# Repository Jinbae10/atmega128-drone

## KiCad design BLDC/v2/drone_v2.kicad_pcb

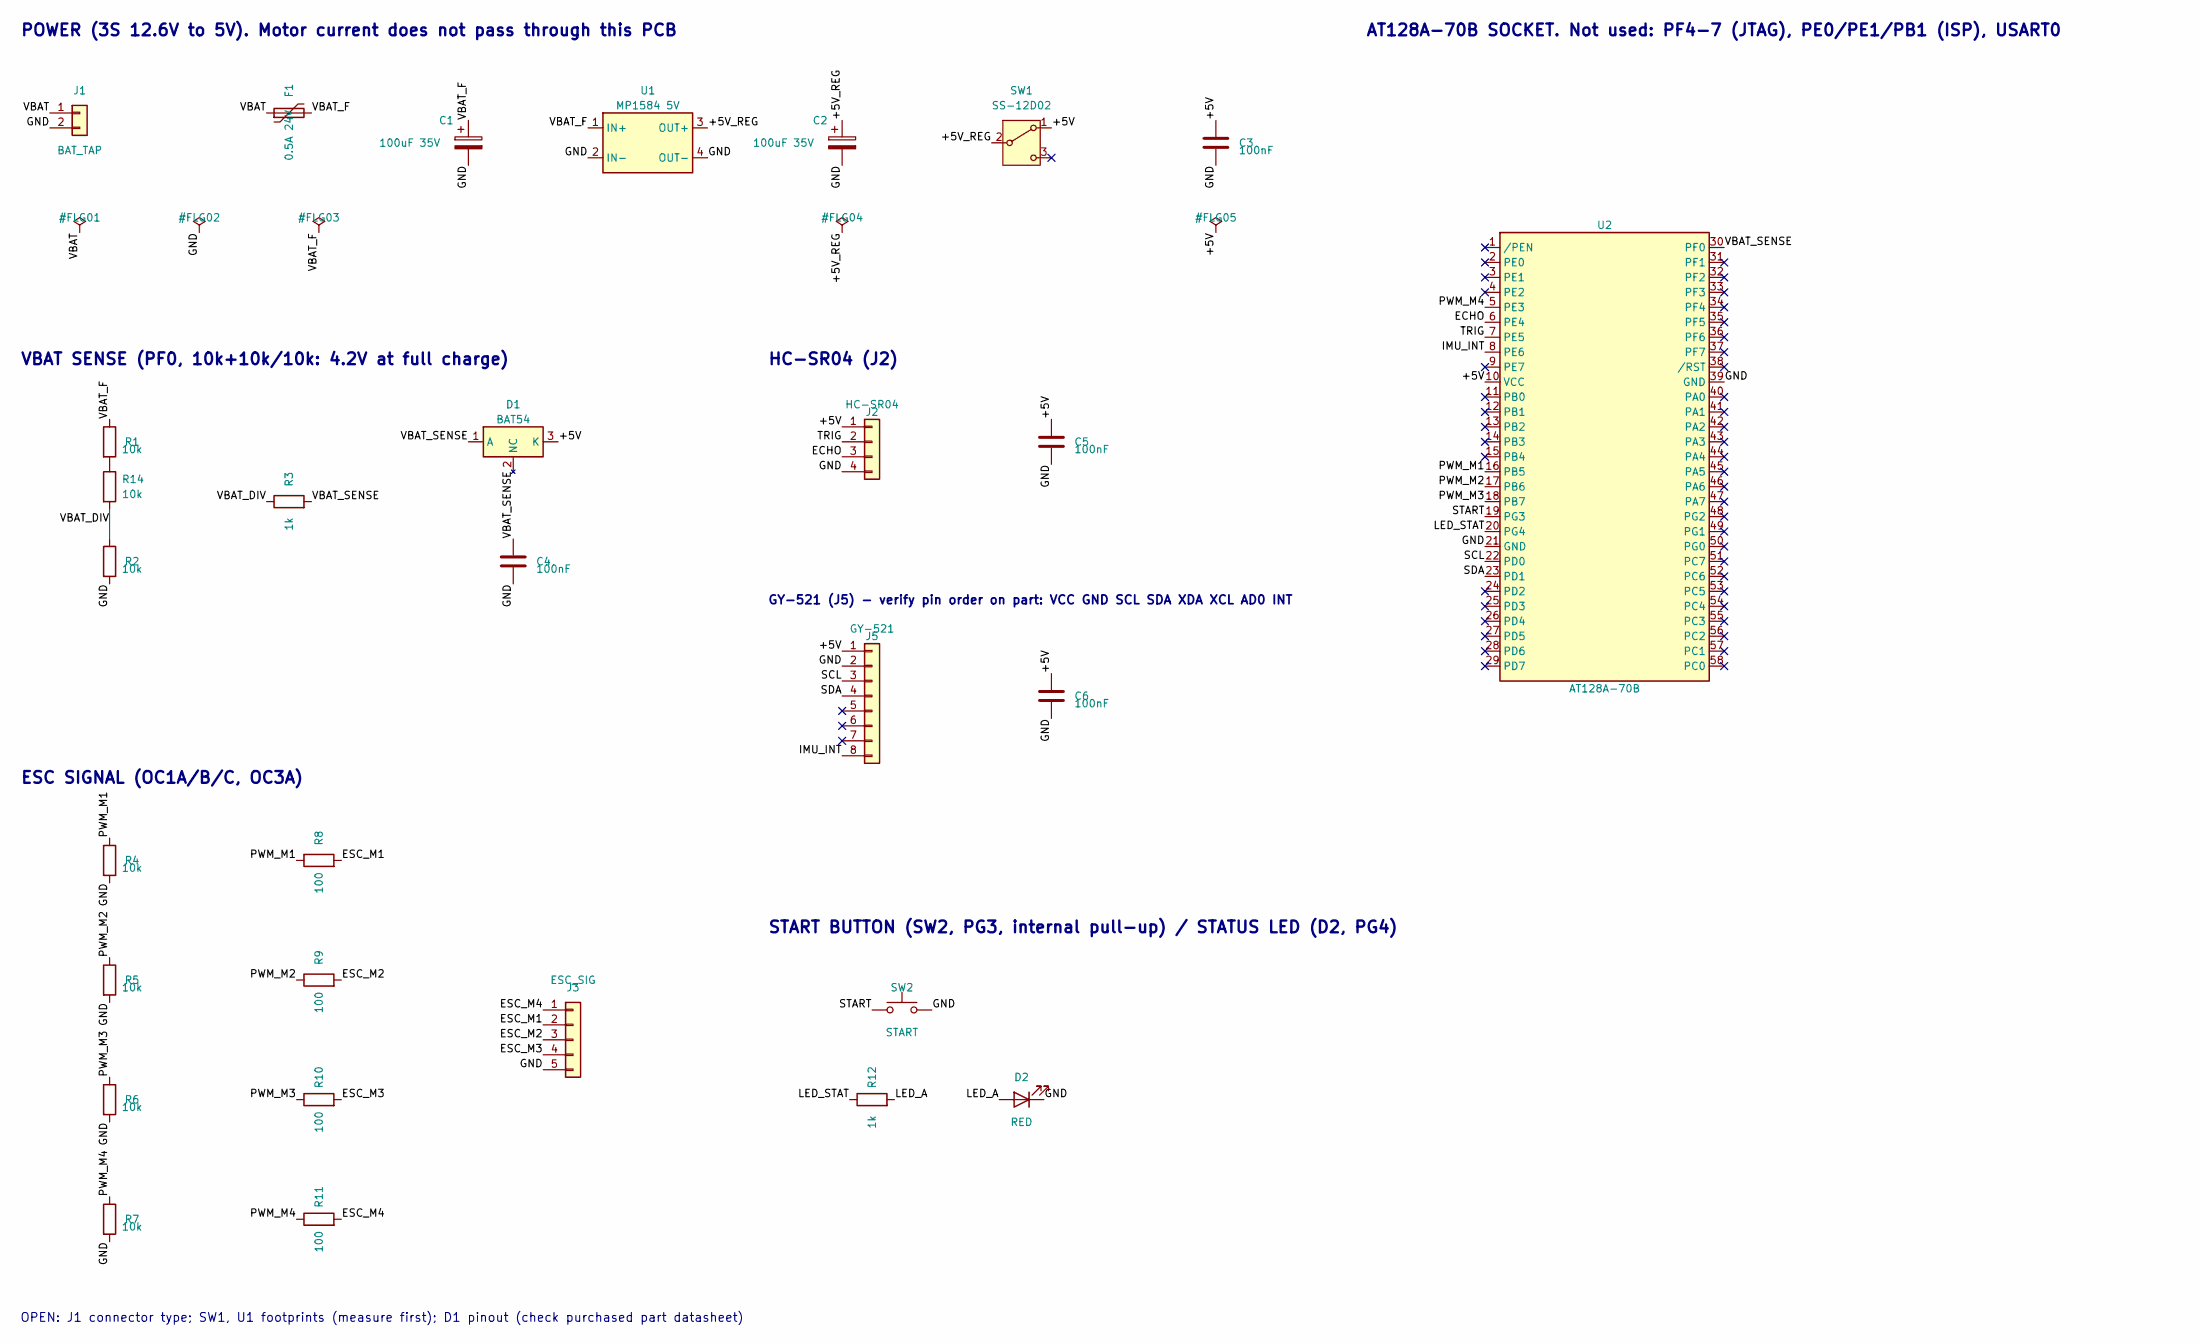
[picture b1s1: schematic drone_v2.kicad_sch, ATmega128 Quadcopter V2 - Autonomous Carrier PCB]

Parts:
C1, C2: 100uF 35V; CP_Radial_D6.3mm_P2.50mm
C3, C4, C5, C6: 100nF; C_1206_3216Metric_Pad1.33x1.80mm_HandSolder
D1: BAT54; SOT-23
D2: RED; LED_0805_2012Metric_Pad1.15x1.40mm_HandSolder
F1: 0.5A 24V; Fuse_1206_3216Metric_Pad1.42x1.75mm_HandSolder; MPN FSMD050-24-1206R
J1: BAT_TAP; PinHeader_1x02_P2.54mm_Vertical
J2: HC-SR04; PinSocket_1x04_P2.54mm_Vertical
J3: ESC_SIG; PinHeader_1x05_P2.54mm_Vertical
J5: GY-521; PinSocket_1x08_P2.54mm_Vertical
R1, R2, R4, R5, R6, R7, R14: 10k; R_0805_2012Metric_Pad1.20x1.40mm_HandSolder
R3, R12: 1k; R_0805_2012Metric_Pad1.20x1.40mm_HandSolder
R8, R9, R10, R11: 100; R_0805_2012Metric_Pad1.20x1.40mm_HandSolder
SW1: SS-12D02; SW_SS-12D02_P2.54
SW2: START; SW_PUSH_6mm
U1: MP1584 5V; MP1584_Module_22x17
U2: AT128A-70B; AT128A-70B_Socket

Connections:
+5V: C3.1, C5.1, C6.1, D1.3 (K), J2.1, J5.1, SW1.1 (A), U2.10 (VCC)
+5V_REG: C2.1, SW1.2 (B), U1.3 (OUT+)
ECHO: J2.3, U2.6 (PE4)
ESC_M1: J3.2, R8.2
ESC_M2: J3.3, R9.2
ESC_M3: J3.4, R10.2
ESC_M4: J3.1, R11.2
GND: C1.2, C2.2, C3.2, C4.2, C5.2, C6.2, D2.1 (K), J1.2, J2.4, J3.5, J5.2, R2.2, R4.2, R5.2, R6.2, R7.2, SW2.2, U1.2 (IN-), U1.4 (OUT-), U2.21 (GND), U2.39 (GND)
IMU_INT: J5.8, U2.8 (PE6)
LED_A: D2.2 (A), R12.2
LED_STAT: R12.1, U2.20 (PG4)
unnamed: R1.2, R14.1
PWM_M1: R4.1, R8.1, U2.16 (PB5)
PWM_M2: R5.1, R9.1, U2.17 (PB6)
PWM_M3: R6.1, R10.1, U2.18 (PB7)
PWM_M4: R7.1, R11.1, U2.5 (PE3)
SCL: J5.3, U2.22 (PD0)
SDA: J5.4, U2.23 (PD1)
START: SW2.1, U2.19 (PG3)
TRIG: J2.2, U2.7 (PE5)
VBAT: F1.1, J1.1
VBAT_DIV: R2.1, R3.1, R14.2
VBAT_F: C1.1, F1.2, R1.1, U1.1 (IN+)
VBAT_SENSE: C4.1, D1.1 (A), R3.2, U2.30 (PF0)

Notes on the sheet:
POWER (3S 12.6V to 5V). Motor current does not pass through this PCB
VBAT SENSE (PF0, 10k+10k/10k: 4.2V at full charge)
ESC SIGNAL (OC1A/B/C, OC3A)
HC-SR04 (J2)
GY-521 (J5) - verify pin order on part: VCC GND SCL SDA XDA XCL AD0 INT
AT128A-70B SOCKET. Not used: PF4-7 (JTAG), PE0/PE1/PB1 (ISP), USART0
OPEN: J1 connector type; SW1, U1 footprints (measure first); D1 pinout (check purchased part datasheet)
START BUTTON (SW2, PG3, internal pull-up) / STATUS LED (D2, PG4)

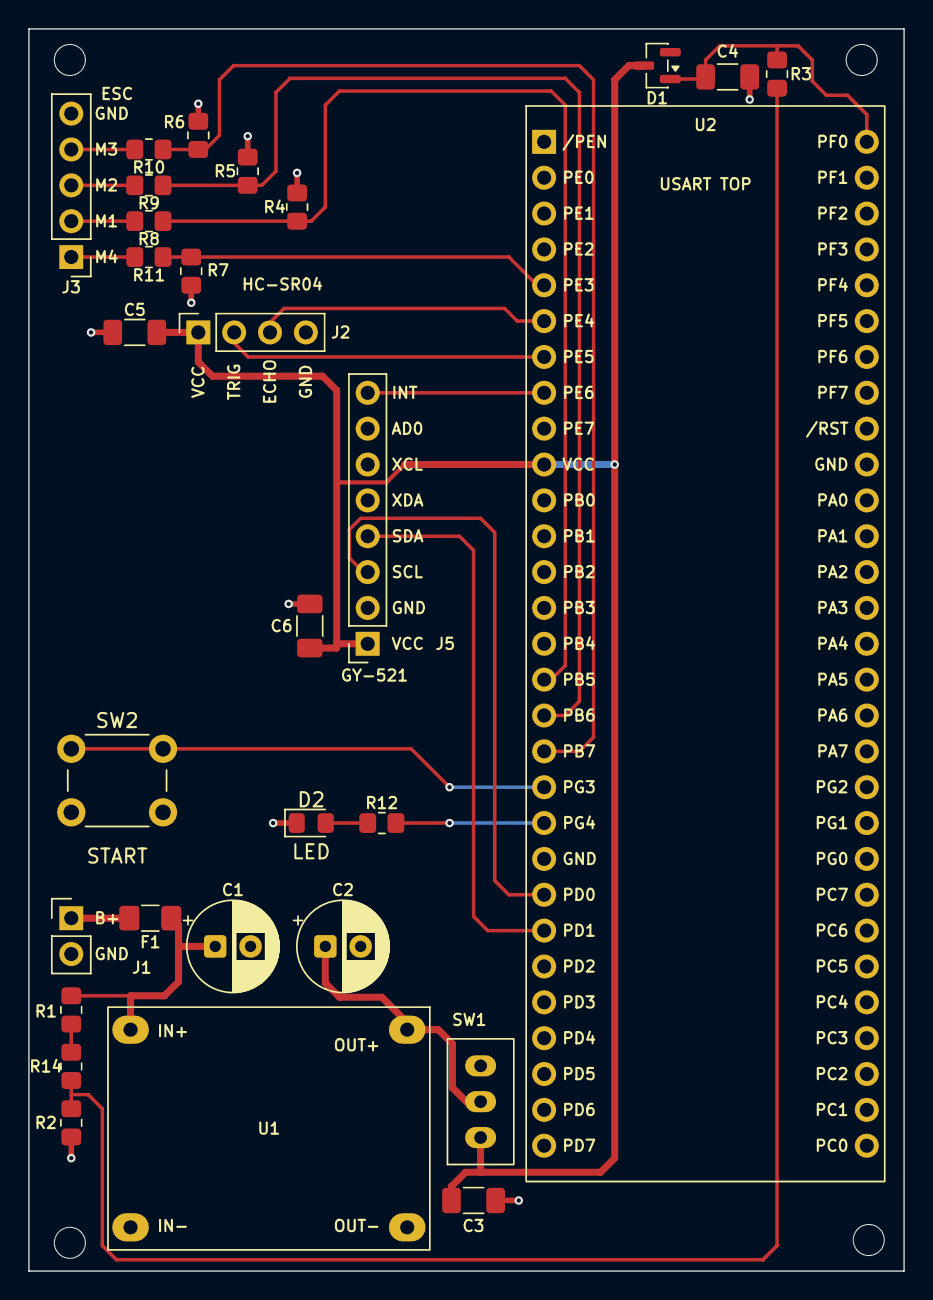
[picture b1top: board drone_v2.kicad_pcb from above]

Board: 2 copper layers, 62.0 x 88.0 mm, 34 parts (0 on the bottom side), 24 nets.

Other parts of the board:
MH1, MH2, MH3, MH4: MountingHole_2.2mm; MountingHole_2.2mm_M2

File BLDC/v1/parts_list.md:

# 부품 목록 (BLDC v1, 3S)

- 기준일: 2026-11-06. 소자 값·수량은 회로도 [drone_v1.kicad_sch](drone_v1.kicad_sch) 기준입니다.
- 가격은 디바이스마트 화면 표시 금액이며, 부가세 별도일 가능성이 있습니다. 재고와 가격은 주문 시 다시 확인해야 합니다.
- 칩 크기는 미터 표기(인치 표기)입니다. 예: 2012(0805).

## 1. 구매할 납땜 소자 (디바이스마트)

| 소자 | 값·정격 | 크기 | 필요 수량 | 회로도 번호 | 품목 | 판매 단위 | 가격 |
|---|---|---|---|---|---|---|---|
| 칩저항 | 10k ±1% (F급) | 2012 | 7 | R1, R2, R14, R4~R7 | TA-I | 100개 | 약 500원 |
| 칩저항 | 1k ±5% (J급) | 2012 | 2 | R3, R12 | TA-I | 100개 | 약 500원 |
| 칩저항 | 2k ±5% (J급) | 2012 | 1 | R13 | TA-I | 100개 | 약 500원 |
| 칩저항 | 100Ω ±5% (J급) | 2012 | 4 | R8~R11 | TA-I | 100개 | 약 500원 |
| MLCC | 100nF | 3216 (1206) | 5 | C3~C7 | 미정 | 100개 | 약 1,900원 |
| 폴리퓨즈 | 0.5A 24V | 3216 (1206) | 1 | F1 | FSMD050-24-1206R | 10개 | 약 1,100원 |
| 쇼트키 다이오드 | BAT54 | SOT-23 | 1 | D1 | Diotec (재판매, 5~7일) | 미확인 | 240원 |
| 전해 커패시터 | 100µF 35V | 스루홀 Ø6.3×11mm, 핀 간격 2.5mm | 2 | C1, C2 | 미정 | 10개 | 약 400원 |
| 슬라이드 스위치 | SPDT 약 0.3A | 스루홀 약 8.7×4.5mm, 핀 간격 2.54mm (미확인) | 1 | SW1 | SS-12D02 | 낱개 | 150원 |
| 핀헤더 | 2.54mm 1×40 | 스루홀 | 1줄 (11핀 사용) | J1, J3, U1 장착용 | 미정 | 낱개 | 200원 |

20k 칩저항은 소량 구매가 어려워 10k 두 개를 직렬로 씁니다(R1 + R14).

## 2. 구매할 모듈·기타 (디바이스마트)

| 부품 | 수량 | 크기 | 품목 | 가격 | 비고 |
|---|---|---|---|---|---|
| MPU-6050 GY-521 | 1 | 약 21×16×3mm | | 4,950원 | 10월 17일 가격. 최근 검색 화면은 4,500원 |
| HC-06 DIP 슬레이브 | 1 | 약 37×17mm (미확인) | SZH-EK105 | 6,050원 | 10월 17일 가격. 최근 검색 화면은 5,500원 |
| MP1584 강압 모듈 | 1 | 약 22×17×4mm (패드 간격 미확인) | VLT-VC042 | 1,800원 | 핀헤더로 PCB에 장착 |
| XT60 암수 세트 | 2 | | | 3,200원 | 2세트 합계로 계산함. 주문 시 확인 |
| 14AWG 실리콘 전선 | 1m | | DFROBOT FIT0583 | 약 9,800원 | 모터 전류 경로 |
| 벨크로 타이 | 1 | | SZ-XL036 | 900원 | 배터리 고정 |
| M3 나사 | 100개 | M3×5 확인, 길이는 모터 실측 후 결정 | | 약 1,000원 | 프레임 확인 후 구매 |
| 열수축 튜브 | 소량 | 지름은 전선에 맞춰 선택 | | 미확인 | |
| 3S LiPo | 1 | 미확인 | 1600mAh 65C | 26,000원 | 프레임 무게 확인 후 결정 |

### 디바이스마트 예상 합계 (표시 가격, 판매 단위 기준)

| 구분 | 금액 |
|---|---|
| 1번 표 합계 | 5,990원 |
| 2번 표 합계 (열수축 튜브·배터리 제외) | 27,700원 |
| **소계** | **33,690원** |
| 3S LiPo 포함 | 59,690원 |

배송비 2,700원과 열수축 튜브는 빠져 있습니다.

## 3. 다른 곳에서 구할 것

| 부품 | 구입처 | 비고 |
|---|---|---|
| 3S 밸런스 충전기 | RC 샵 | 디바이스마트 검색에서 못 찾음 |
| 전원 분배 보드 (40A 이상, 4출력) | RC 샵 | ESC 전해가 없거나 16V면 35V 470µF 추가 |
| LiPo 가방 | RC 샵 | |
| 와트미터 50A 이상 | RC 샵 | 권장 품목 |
| PCB 2층 0.8mm | JLCPCB | 설계 완료 후 주문 |
| 프레임 | 학교 3D 프린터 | STL 미선정 |

## 4. 아직 정하지 않은 것

| 항목 | 상태 |
|---|---|
| 플럭스, 핀셋, 솔더윅 | SMD 납땜에 필요. 대여 공구함에 있는지 미확인 |
| 로직 배선 24~26AWG | 실험실 여분 확인. 디바이스마트 26AWG는 60m 키트(22,000원)라 소량용으로 맞지 않음 |
| J1(로직 전원) 커넥터·케이블 | 회로도는 임시로 2.54mm 2핀 헤더 |
| J2(HC-SR04)·J4(HC-06) 연결 케이블 | PCB 쪽이 소켓이므로 모듈 핀과 맞는 4선 케이블 필요 |
| J3(ESC 신호) 연결 케이블 | PCB 쪽이 5핀 헤더. ESC 신호선 끝단 확인 필요 |
| M2 나사·스페이서 | PCB M2 구멍 4개용. 프레임 확정 후 길이 결정 |
| 여분 프로펠러 | 총 8개 권장. 구매 수량 확인 후 결정 |
| 프로펠러 가드 | 미결정 |

## 5. 이미 있는 것 (구매 불필요)

| 부품 | 수량 | 크기 | 상태 |
|---|---|---|---|
| BLDC 모터 2204 | 4 | | 구매 완료 |
| ESC | 4 | | 구매 완료, BEC 미사용 |
| 프로펠러 | 구매 수량 | | 구매 완료 |
| AT128A-70B 모듈 | 1 | 25.4×76.2mm | 대여, 납땜·개조 금지 |
| HC-SR04 | 1 | 약 45×20×15mm (미확인) | 보유 |
| 2.54mm 암헤더 1×40 | 2줄 | 스루홀 | 보유, **수량 확인 필요** (아래 참고) |
| USB JTAG ICE | 1 | | 대여 |
| AR-UART2USB + 케이블 | 1 | | 대여 |
| 납땜 공구 | 1식 | | 대여 |

**암헤더 수량:** 소켓은 29핀 2개(모듈), 8핀 1개(GY-521), 4핀 2개(HC-SR04·HC-06)로 총 74핀이 필요합니다. 자를 때 1칸씩 손실되므로 1×40 1줄에서 29핀+8핀, 다른 1줄에서 29핀+4핀+4핀을 자르면 2줄로 충분합니다(계산값).

## 주문 전 실측·확인

- MP1584(VLT-VC042) 패드 위치, SS-12D02 핀 간격, GY-521 헤더 위치, HC-06 핀 순서: 현재 PCB 풋프린트는 동종 제품 치수를 기준으로 한 값이라 실물과 다를 수 있습니다.
- 3216 MLCC의 전압 정격: 품목을 고르지 않았습니다. C3~C7은 5V 이하 회로에 들어갑니다.
- 2012 저항의 정격 전력: 1/8W는 일반값이며 구매 품목 표기로 확인하지 않았습니다.
- 모터·ESC·프로펠러의 실제 모델: 구매 내역을 보지 못했습니다.

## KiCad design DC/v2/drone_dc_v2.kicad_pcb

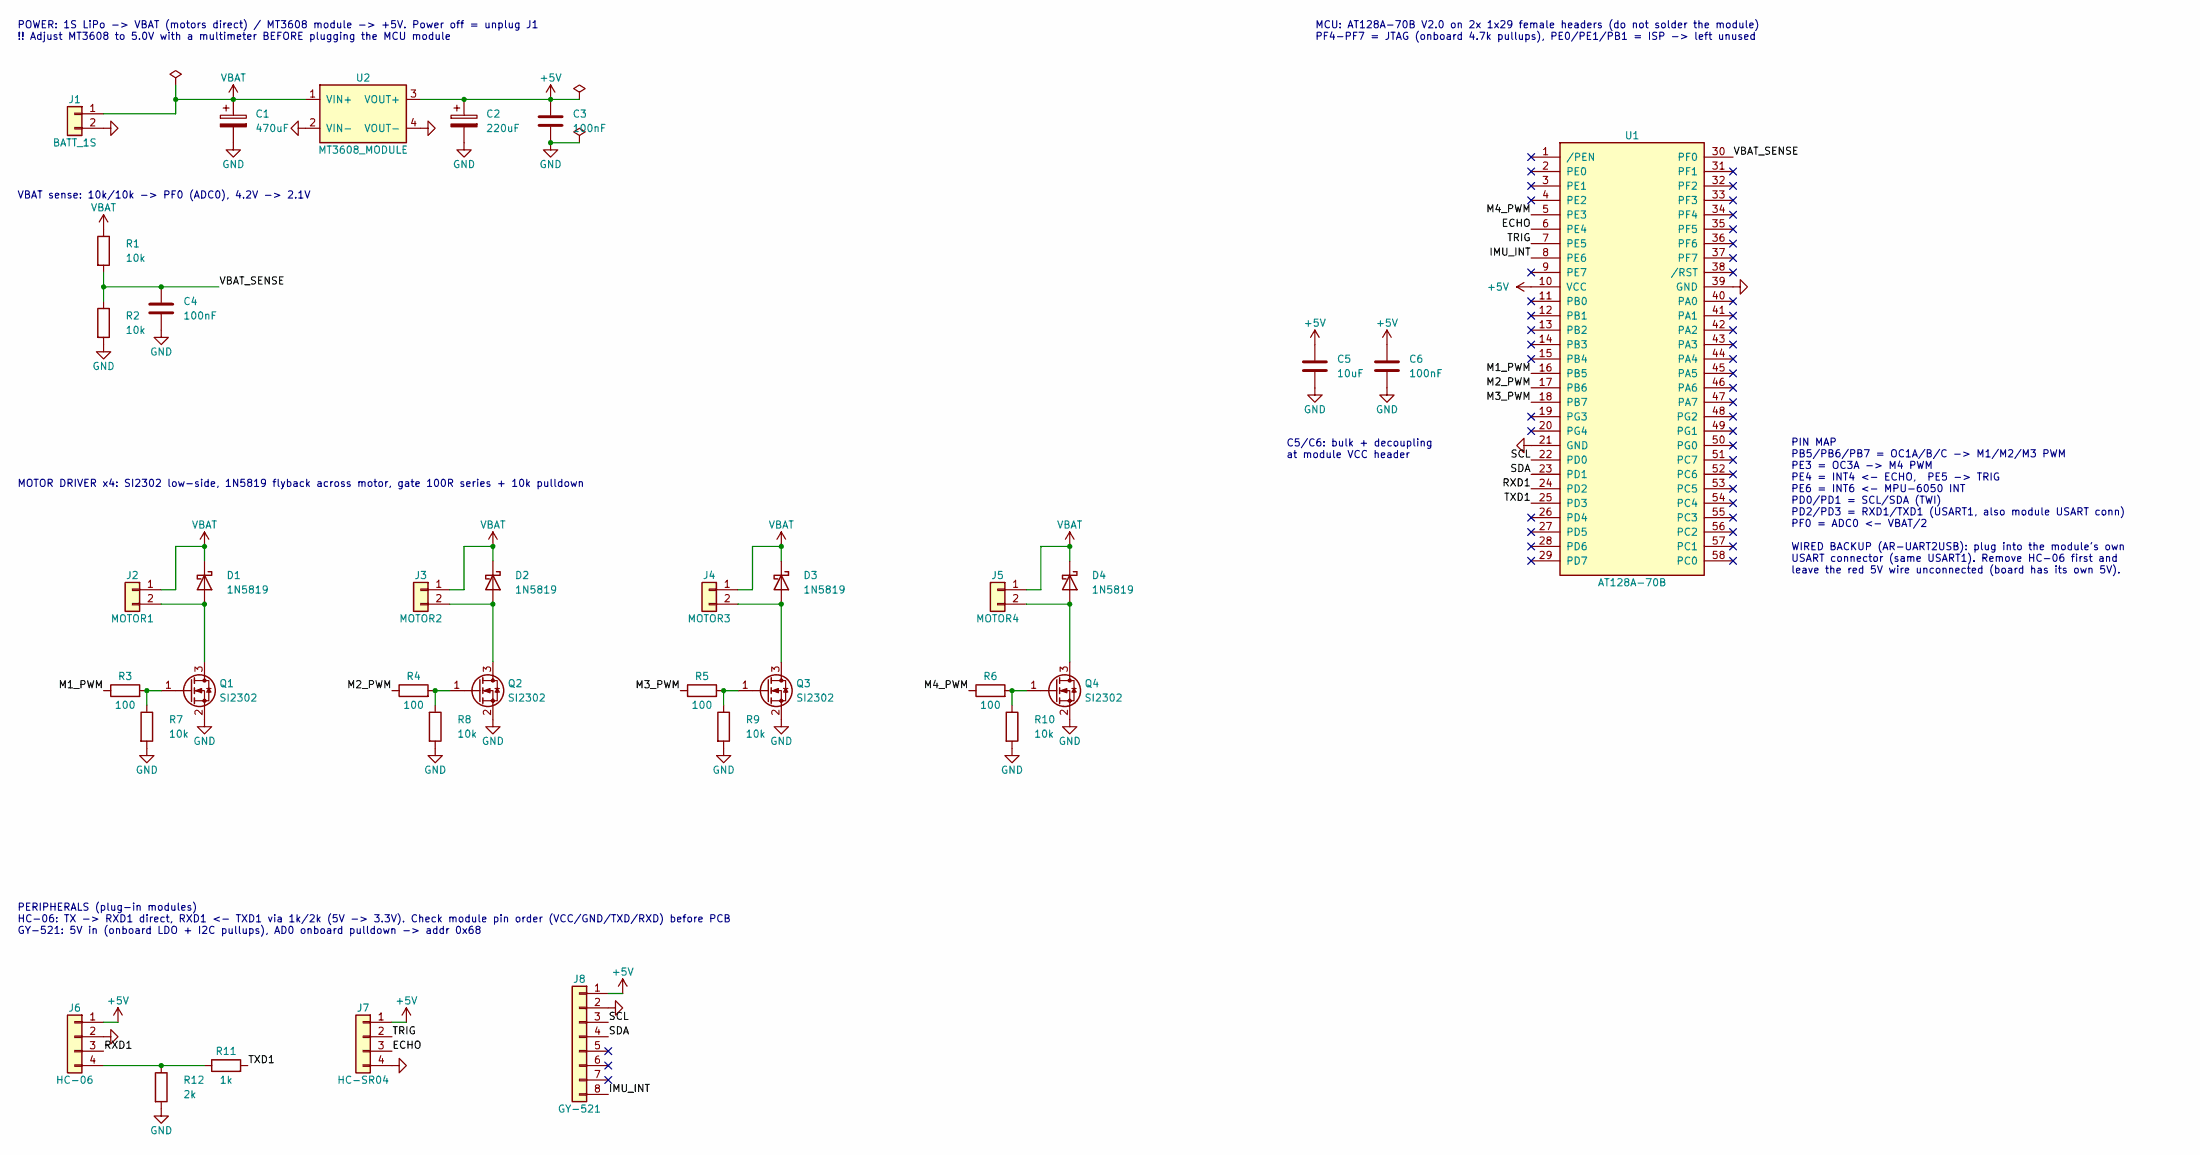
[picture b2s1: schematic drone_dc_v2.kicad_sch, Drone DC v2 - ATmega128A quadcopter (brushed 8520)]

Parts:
C1: 470uF; CP_Radial_D8.0mm_P3.50mm
C2: 220uF; CP_Radial_D6.3mm_P2.50mm
C3, C4, C6: 100nF; C_Disc_D3.0mm_W1.6mm_P2.50mm
C5: 10uF; CP_Radial_D5.0mm_P2.00mm
D1, D2, D3, D4: 1N5819; D_DO-41_SOD81_P5.08mm_Vertical_AnodeUp
J1: BATT_1S; JST_PH_B2B-PH-K_1x02_P2.00mm_Vertical
J2: MOTOR1; PinHeader_1x02_P2.54mm_Vertical
J3: MOTOR2; PinHeader_1x02_P2.54mm_Vertical
J4: MOTOR3; PinHeader_1x02_P2.54mm_Vertical
J5: MOTOR4; PinHeader_1x02_P2.54mm_Vertical
J6: HC-06; PinSocket_1x04_P2.54mm_Vertical
J7: HC-SR04; PinSocket_1x04_P2.54mm_Vertical
J8: GY-521; PinSocket_1x08_P2.54mm_Vertical
Q1, Q2, Q3, Q4: SI2302; SOT-23_Handsoldering
R1, R2, R7, R8, R9, R10: 10k; R_Axial_DIN0207_L6.3mm_D2.5mm_P2.54mm_Vertical
R3, R4, R5, R6: 100; R_Axial_DIN0207_L6.3mm_D2.5mm_P2.54mm_Vertical
R11: 1k; R_Axial_DIN0207_L6.3mm_D2.5mm_P2.54mm_Vertical
R12: 2k; R_Axial_DIN0207_L6.3mm_D2.5mm_P2.54mm_Vertical
U1: AT128A-70B; AT128A-70B_Module
U2: MT3608_MODULE; MT3608_Module_Wire

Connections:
+5V: C2.1, C3.1, C5.1, C6.1, J6.1, J7.1, J8.1, U1.10 (VCC), U2.3 (VOUT+)
/ECHO: J7.3, U1.6 (PE4)
/IMU_INT: J8.8, U1.8 (PE6)
/M1_PWM: R3.1, U1.16 (PB5)
/M2_PWM: R4.1, U1.17 (PB6)
/M3_PWM: R5.1, U1.18 (PB7)
/M4_PWM: R6.1, U1.5 (PE3)
/RXD1: J6.3, U1.24 (PD2)
/SCL: J8.3, U1.22 (PD0)
/SDA: J8.4, U1.23 (PD1)
/TRIG: J7.2, U1.7 (PE5)
/TXD1: R11.2, U1.25 (PD3)
/VBAT_SENSE: C4.1, R1.2, R2.1, U1.30 (PF0)
GND: C1.2, C2.2, C3.2, C4.2, C5.2, C6.2, J1.2, J6.2, J7.4, J8.2, Q1.2 (S), Q2.2 (S), Q3.2 (S), Q4.2 (S), R2.2, R7.2, R8.2, R9.2, R10.2, R12.2, U1.21 (GND), U1.39 (GND), U2.2 (VIN-), U2.4 (VOUT-)
unnamed: D1.2 (A), J2.2, Q1.3 (D)
unnamed: D2.2 (A), J3.2, Q2.3 (D)
unnamed: D3.2 (A), J4.2, Q3.3 (D)
unnamed: D4.2 (A), J5.2, Q4.3 (D)
unnamed: J6.4, R11.1, R12.1
unnamed: Q1.1 (G), R3.2, R7.1
unnamed: Q2.1 (G), R4.2, R8.1
unnamed: Q3.1 (G), R5.2, R9.1
unnamed: Q4.1 (G), R6.2, R10.1
VBAT: C1.1, D1.1 (K), D2.1 (K), D3.1 (K), D4.1 (K), J1.1, J2.1, J3.1, J4.1, J5.1, R1.1, U2.1 (VIN+)

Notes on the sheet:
POWER: 1S LiPo -> VBAT (motors direct) / MT3608 module -> +5V. Power off = unplug J1 !! Adjust MT3608 to 5.0V with a multimeter BEFORE plugging the MCU module
VBAT sense: 10k/10k -> PF0 (ADC0), 4.2V -> 2.1V
MOTOR DRIVER x4: SI2302 low-side, 1N5819 flyback across motor, gate 100R series + 10k pulldown
PERIPHERALS (plug-in modules) HC-06: TX -> RXD1 direct, RXD1 <- TXD1 via 1k/2k (5V -> 3.3V). Check module pin order (VCC/GND/TXD/RXD) before PCB GY-521: 5V in (onboard LDO + I2C pullups), AD0 onboard pulldown -> addr 0x68
MCU: AT128A-70B V2.0 on 2x 1x29 female headers (do not solder the module) PF4-PF7 = JTAG (onboard 4.7k pullups), PE0/PE1/PB1 = ISP -> left unused
C5/C6: bulk + decoupling at module VCC header
PIN MAP PB5/PB6/PB7 = OC1A/B/C -> M1/M2/M3 PWM PE3 = OC3A -> M4 PWM PE4 = INT4 <- ECHO, PE5 -> TRIG PE6 = INT6 <- MPU-6050 INT PD0/PD1 = SCL/SDA (TWI) PD2/PD3 = RXD1/TXD1 (USART1, also module USART conn) PF0 = ADC0 <- VBAT/2 WIRED BACKUP (AR-UART2USB): plug into the module's own USART connector (sa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

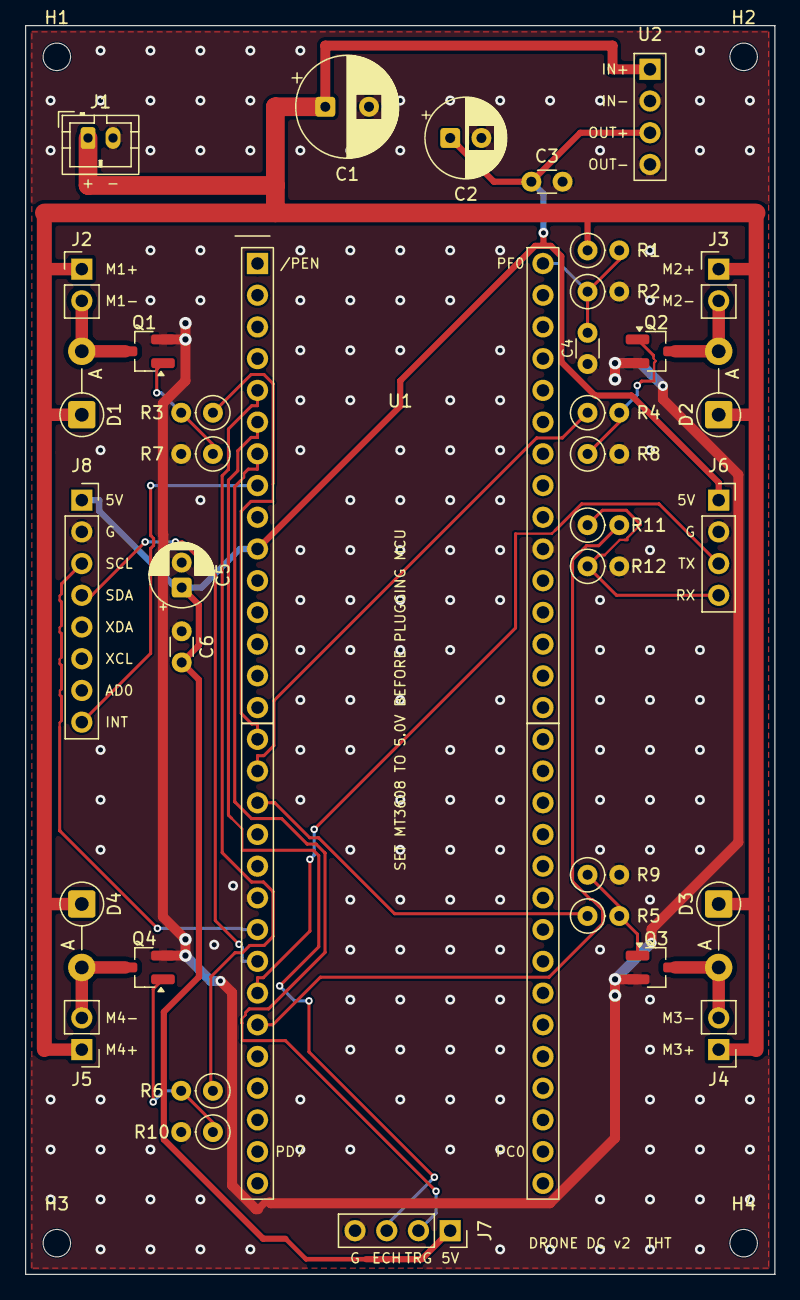
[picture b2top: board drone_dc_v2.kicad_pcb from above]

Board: 2 copper layers, 60.0 x 100.0 mm, 40 parts (0 on the bottom side), 24 nets.

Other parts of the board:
H1, H2, H3, H4: M2; MountingHole_2.2mm_M2

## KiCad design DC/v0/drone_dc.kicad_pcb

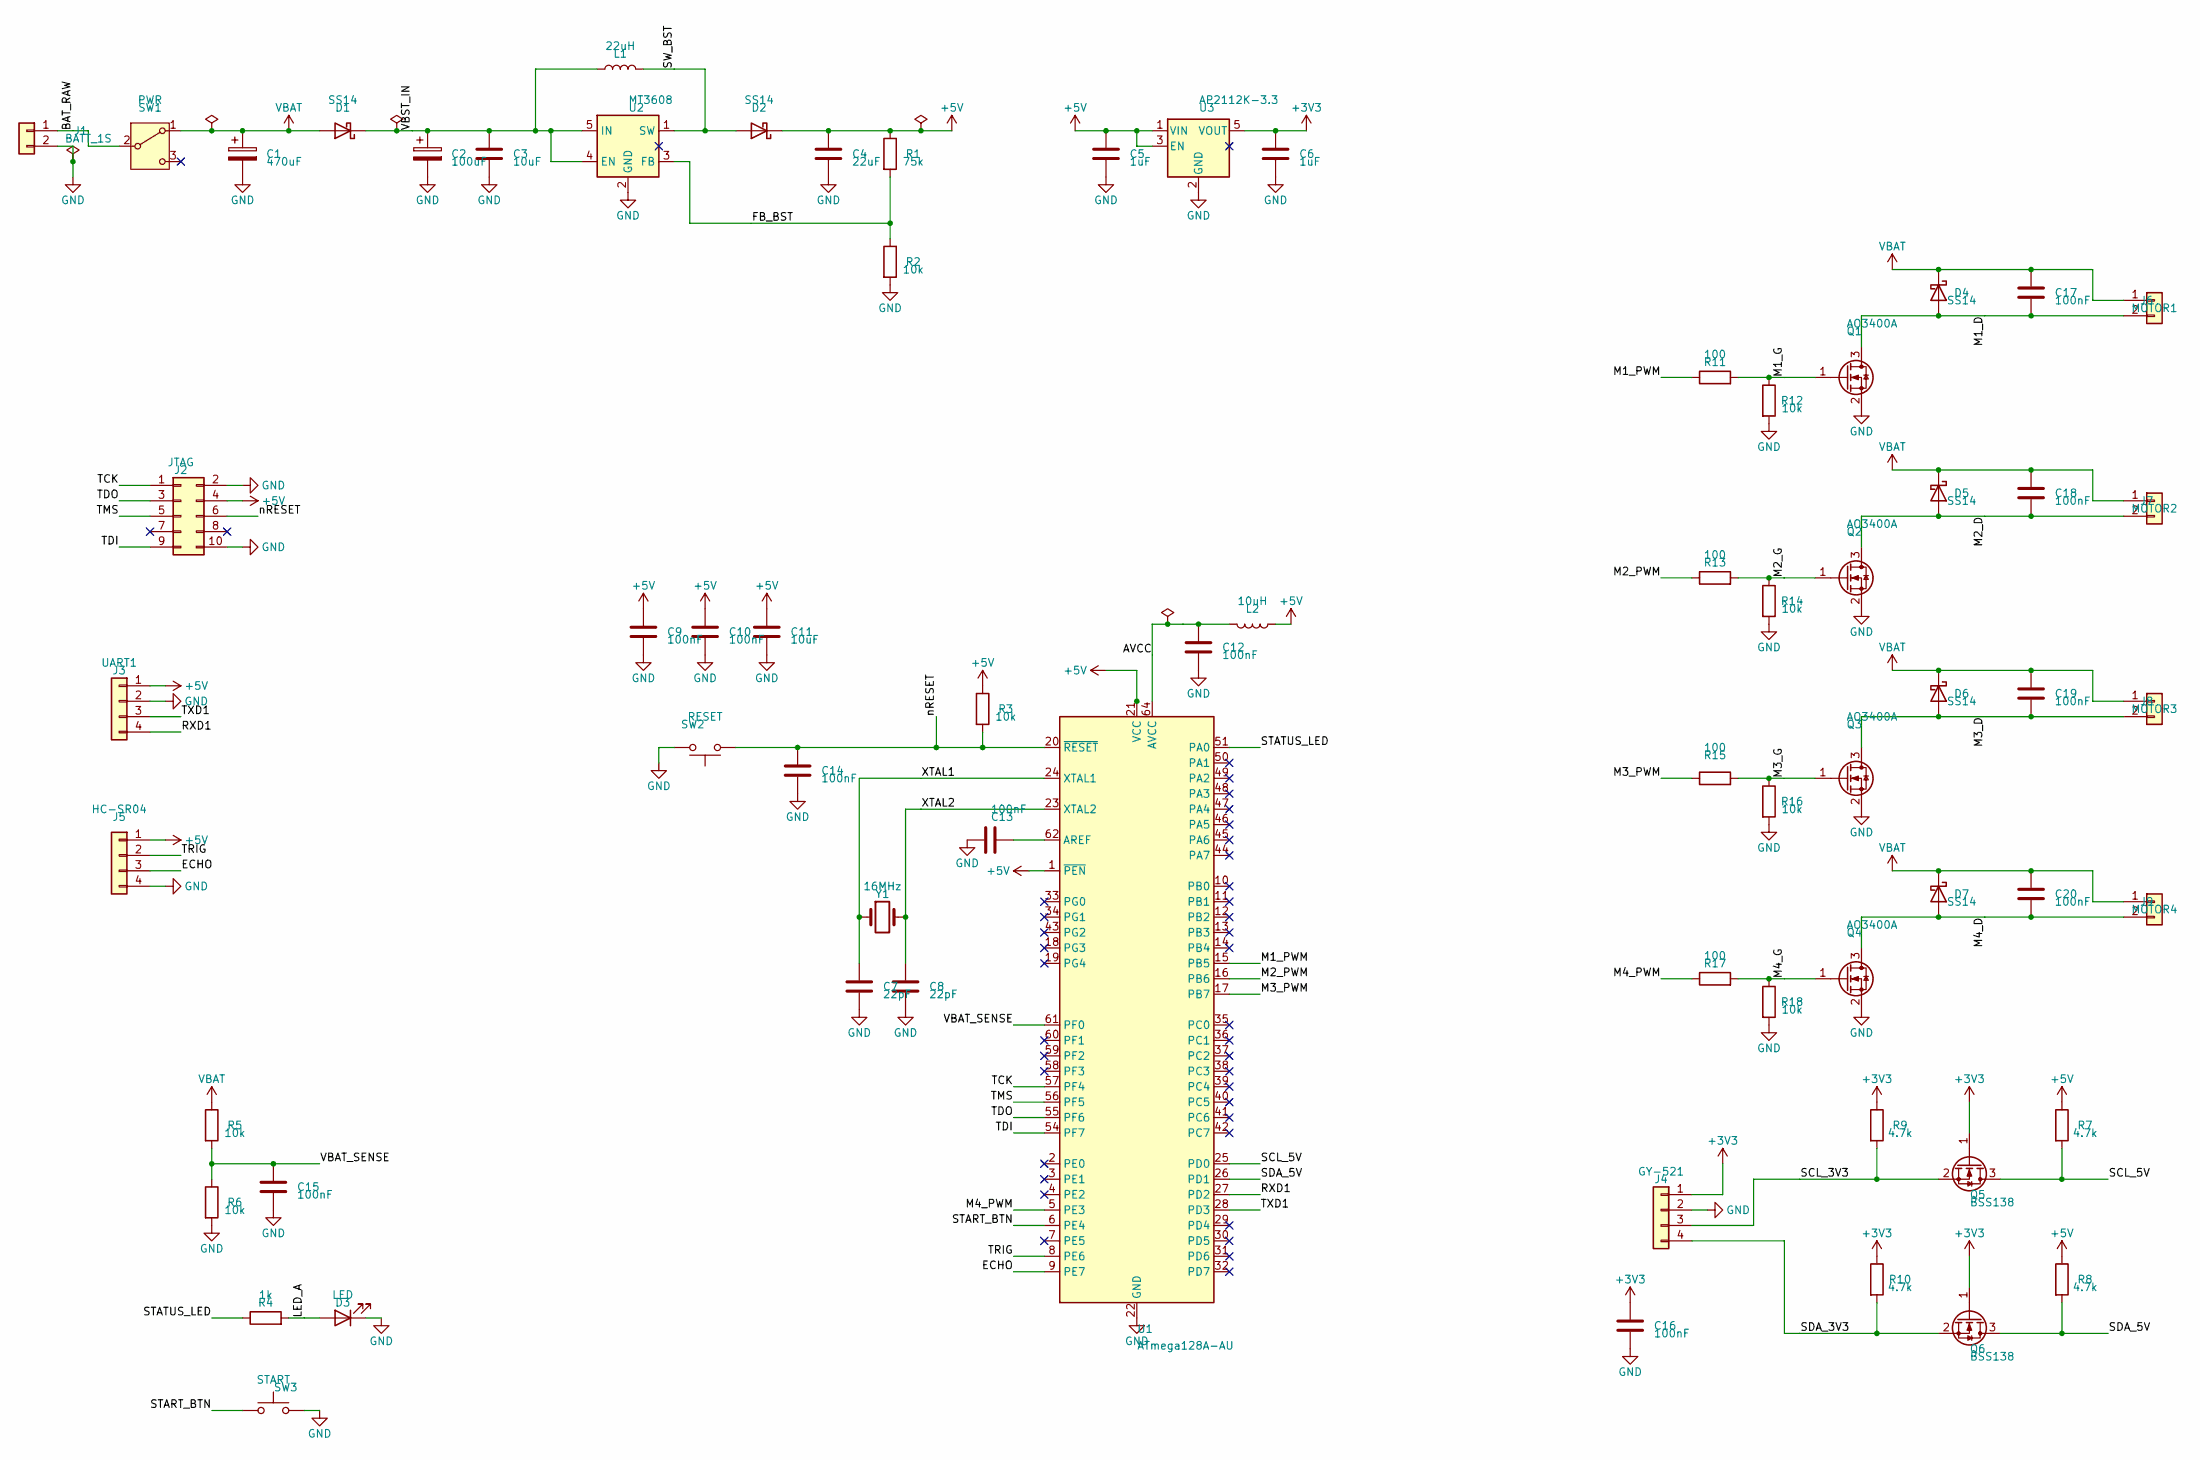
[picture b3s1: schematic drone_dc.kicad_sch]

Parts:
C1: 470uF; CP_Elec_8x10
C2: 100uF; CP_Elec_6.3x7.7
C3, C11: 10uF; C_0805_2012Metric
C4: 22uF; C_0805_2012Metric
C5, C6: 1uF; C_0603_1608Metric
C7, C8: 22pF; C_0603_1608Metric
C9, C10, C12, C13, C14, C15, C16, C17, C18, C19, C20: 100nF; C_0603_1608Metric
D1, D2, D4, D5, D6, D7: SS14; D_SMA
D3: LED; LED_0603_1608Metric
J1: BATT_1S; JST_PH_B2B-PH-K_1x02_P2.00mm_Vertical
J2: JTAG; PinHeader_2x05_P2.54mm_Vertical
J3: UART1; PinHeader_1x04_P2.54mm_Vertical
J4: GY-521; PinHeader_1x04_P2.54mm_Vertical
J5: HC-SR04; PinHeader_1x04_P2.54mm_Vertical
J6: MOTOR1; JST_PH_B2B-PH-K_1x02_P2.00mm_Vertical
J7: MOTOR2; JST_PH_B2B-PH-K_1x02_P2.00mm_Vertical
J8: MOTOR3; JST_PH_B2B-PH-K_1x02_P2.00mm_Vertical
J9: MOTOR4; JST_PH_B2B-PH-K_1x02_P2.00mm_Vertical
L1: 22uH; L_Bourns_SRN6045TA
L2: 10uH; L_0805_2012Metric
Q1, Q2, Q3, Q4: AO3400A; SOT-23
Q5, Q6: BSS138; SOT-23
R1: 75k; R_0603_1608Metric
R2, R3, R5, R6, R12, R14, R16, R18: 10k; R_0603_1608Metric
R4: 1k; R_0603_1608Metric
R7, R8, R9, R10: 4.7k; R_0603_1608Metric
R11, R13, R15, R17: 100; R_0603_1608Metric
SW1: PWR; SW_SPDT_PCM12
SW2: RESET; SW_SPST_TL3342
SW3: START; SW_SPST_TL3342
U1: ATmega128A-AU; TQFP-64_14x14mm_P0.8mm
U2: MT3608; SOT-23-6
U3: AP2112K-3.3; SOT-23-5
Y1: 16MHz; Crystal_SMD_HC49-SD

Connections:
+3V3: C6.1, C16.1, J4.1, Q5.1 (G), Q6.1 (G), R9.1, R10.1, U3.5 (VOUT)
+5V: C4.1, C5.1, C9.1, C10.1, C11.1, D2.1 (K), J2.4, J3.1, J5.1, L2.1, R1.1, R3.1, R7.1, R8.1, U1.1 (~PEN), U1.21 (VCC), U1.52 (VCC), U3.1 (VIN), U3.3 (EN)
AVCC: C12.1, L2.2, U1.64 (AVCC)
BAT_RAW: J1.1, SW1.2 (B)
ECHO: J5.3, U1.9 (PE7)
FB_BST: R1.2, R2.1, U2.3 (FB)
GND: C1.2, C2.2, C3.2, C4.2, C5.2, C6.2, C7.2, C8.2, C9.2, C10.2, C11.2, C12.2, C13.2, C14.2, C15.2, C16.2, D3.1 (K), J1.2, J2.2, J2.10, J3.2, J4.2, J5.4, Q1.2 (S), Q2.2 (S), Q3.2 (S), Q4.2 (S), R2.2, R6.2, R12.2, R14.2, R16.2, R18.2, SW2.2, SW3.2, U1.22 (GND), U1.53 (GND), U1.63 (GND), U2.2 (GND), U3.2 (GND)
LED_A: D3.2 (A), R4.2
M1_D: C17.2, D4.2 (A), J6.2, Q1.3 (D)
M1_G: Q1.1 (G), R11.2, R12.1
M1_PWM: R11.1, U1.15 (PB5)
M2_D: C18.2, D5.2 (A), J7.2, Q2.3 (D)
M2_G: Q2.1 (G), R13.2, R14.1
M2_PWM: R13.1, U1.16 (PB6)
M3_D: C19.2, D6.2 (A), J8.2, Q3.3 (D)
M3_G: Q3.1 (G), R15.2, R16.1
M3_PWM: R15.1, U1.17 (PB7)
M4_D: C20.2, D7.2 (A), J9.2, Q4.3 (D)
M4_G: Q4.1 (G), R17.2, R18.1
M4_PWM: R17.1, U1.5 (PE3)
unnamed: C13.1, U1.62 (AREF)
RXD1: J3.4, U1.27 (PD2)
SCL_3V3: J4.3, Q5.2 (S), R9.2
SCL_5V: Q5.3 (D), R7.2, U1.25 (PD0)
SDA_3V3: J4.4, Q6.2 (S), R10.2
SDA_5V: Q6.3 (D), R8.2, U1.26 (PD1)
START_BTN: SW3.1, U1.6 (PE4)
STATUS_LED: R4.1, U1.51 (PA0)
SW_BST: D2.2 (A), L1.2, U2.1 (SW)
TCK: J2.1, U1.57 (PF4)
TDI: J2.9, U1.54 (PF7)
TDO: J2.3, U1.55 (PF6)
TMS: J2.5, U1.56 (PF5)
TRIG: J5.2, U1.8 (PE6)
TXD1: J3.3, U1.28 (PD3)
VBAT: C1.1, C17.1, C18.1, C19.1, C20.1, D1.2 (A), D4.1 (K), D5.1 (K), D6.1 (K), D7.1 (K), J6.1, J7.1, J8.1, J9.1, R5.1, SW1.1 (A)
VBAT_SENSE: C15.1, R5.2, R6.1, U1.61 (PF0)
VBST_IN: C2.1, C3.1, D1.1 (K), L1.1, U2.4 (EN), U2.5 (IN)
XTAL1: C7.1, U1.24 (XTAL1), Y1.1
XTAL2: C8.1, U1.23 (XTAL2), Y1.2
nRESET: C14.1, J2.6, R3.2, SW2.1, U1.20 (~RESET)

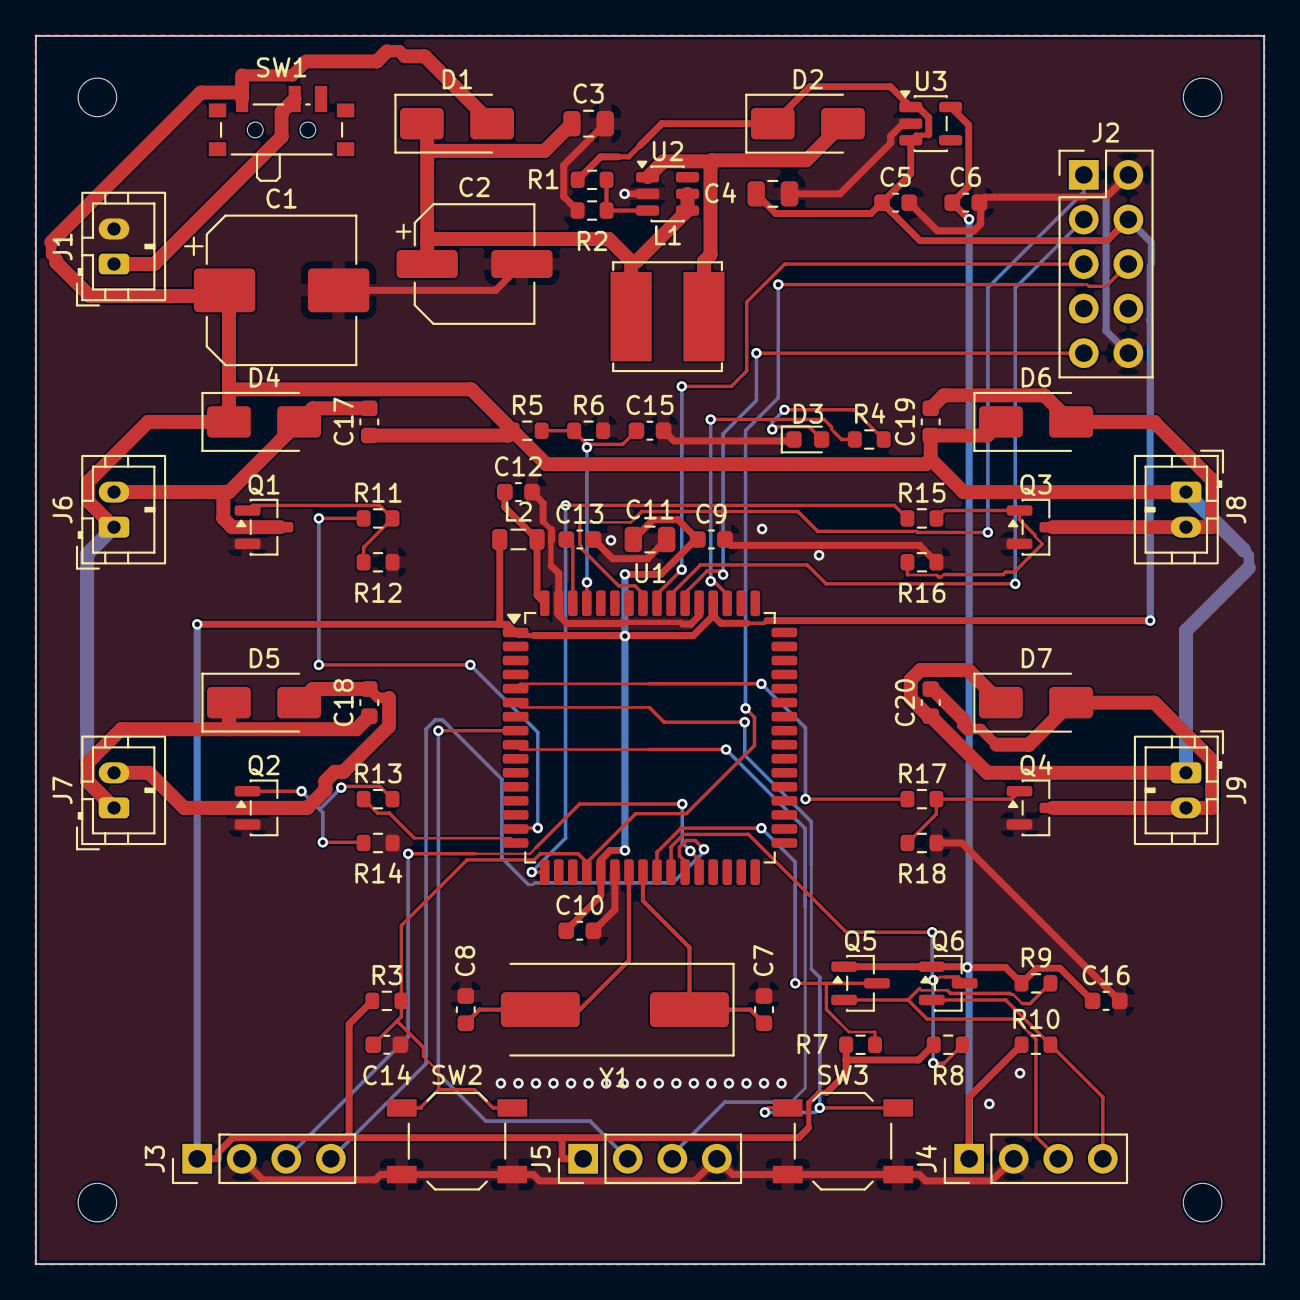
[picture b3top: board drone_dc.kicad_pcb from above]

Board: 2 copper layers, 70.0 x 70.0 mm, 73 parts (0 on the bottom side), 41 nets.

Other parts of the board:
H1, H2, H3, H4: MountingHole_2.2mm_M2
